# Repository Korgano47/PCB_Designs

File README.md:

# PCB_Designs
This repository contains some PCB examples designed by me with Autodesk EAGLE.

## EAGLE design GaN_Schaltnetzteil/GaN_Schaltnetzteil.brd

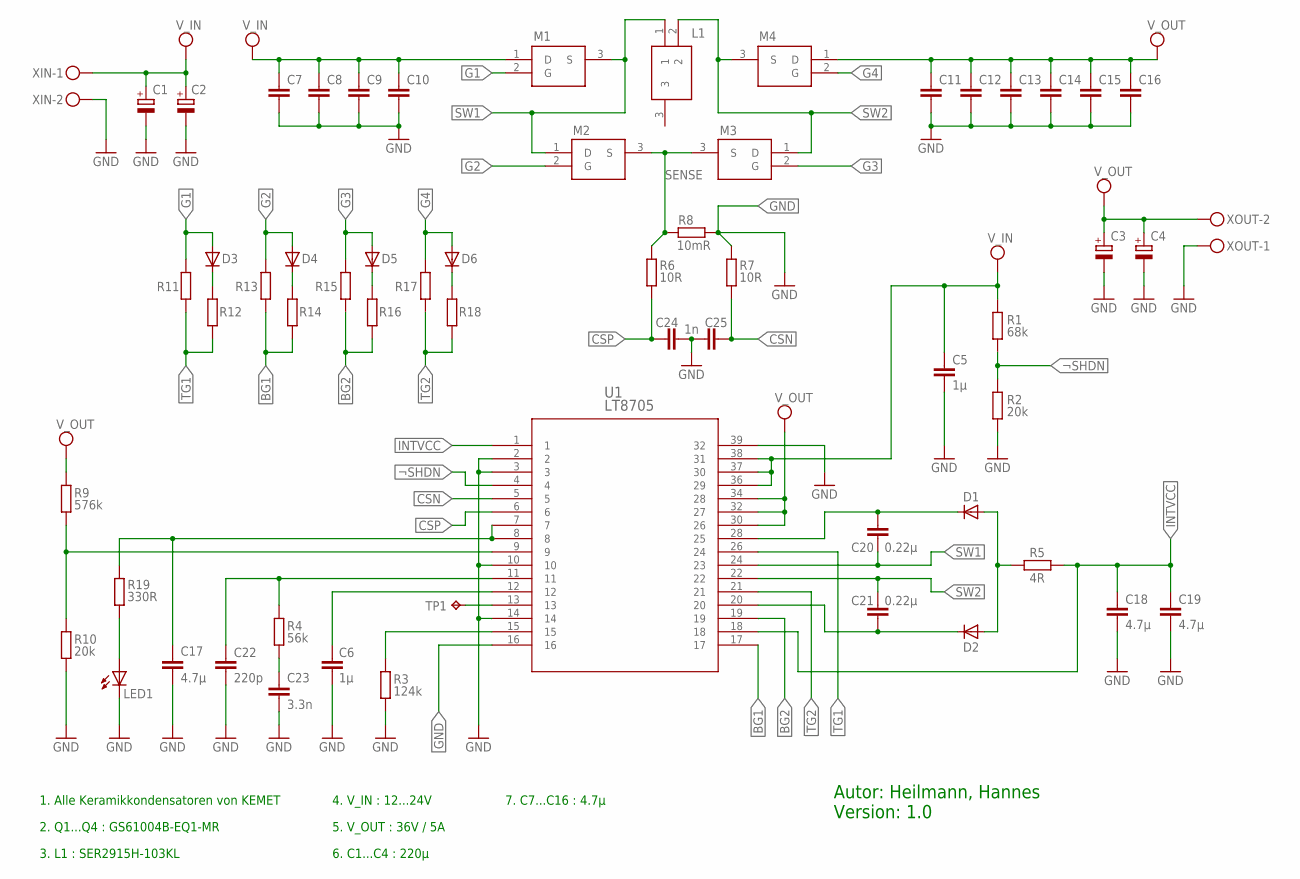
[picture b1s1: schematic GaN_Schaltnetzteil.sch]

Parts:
C1, C2, C3, C4: 220µ; PANASONIC_G
C5, C6: 1µ; C1206K
C7, C8, C9, C10, C11, C12, C13, C14, C15, C16, C17, C18, C19: 4.7µ; C1206K
C20, C21: 0.22µ; C1206K
C22: 220p; C1206K
C23: 3.3n; C1206K
C24, C25: 1n; C1206K
D1, D2, D3, D4, D5, D6: GF1; SMA-DO214AC
L1: SER2915H-103KL; SER2900
LED1: LEDSMT1206; 1206
M1, M2, M3, M4: GS61004B-E01-MR
R1: 68k; R1206
R2, R10: 20k; R1206
R3: 124k; R1206
R4: 56k; R1206
R5: 4R; R1206
R6, R7: 10R; R1206
R8: 10mR; R1206
R9: 576k; R1206
R11, R12, R13, R14, R15, R16, R17, R18: R-EU_R1206; R1206
R19: 330R; R1206
TP1: TPTP08R; TP08R
U1: LT8705; TSSOP-38_FE/AB
XIN: INPUT; W237-102
XOUT: OUTPUT; W237-102

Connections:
BG1: R13.1, R14.1, U1.17
BG2: R15.1, R16.1, U1.19
BOOST1: C20.1, D1.K (C), U1.28 (25)
BOOST2: C21.1, D2.K (C), U1.20
CSN: C25.2, R7.1, U1.5
CSP: C24.1, R6.1, U1.6
G1: D3.A, M1.2 (G), R11.2
G2: D4.A, M2.2 (G), R13.2
G3: D5.A, M3.2 (G), R15.2
G4: D6.A, M4.2 (G), R17.2
GND: C1.-, C2.-, C3.-, C4.-, C5.2, C6.2, C7.2, C8.2, C9.2, C10.2, C11.2, C12.2, C13.2, C14.2, C15.2, C16.2, C17.2, C18.2, C19.2, C22.2, C23.2, C24.2, C25.1, LED1.C, R2.2, R3.1, R7.2, R8.1, R10.2, U1.2, U1.3, U1.10, U1.14, U1.16, U1.39 (32), XIN.2, XOUT.1
INTVCC: C18.1, C19.1, R5.1, U1.1, U1.18
unnamed: LED1.A, R19.1
unnamed: D3.K (C), R12.2
unnamed: D4.K (C), R14.2
unnamed: TP1.TP, U1.13
unnamed: C6.1, U1.12
unnamed: R3.2, U1.15
unnamed: C23.1, R4.2
unnamed: D5.K (C), R16.2
unnamed: C22.1, R4.1, U1.11
unnamed: D6.K (C), R18.2
unnamed: R9.2, R10.1, U1.9
unnamed: D1.A, D2.A, R5.2
unnamed: C17.1, R19.2, U1.7, U1.8
SENSE: M2.3 (S), M3.3 (S), R6.2, R8.2
SW1: C20.2, L1.1, M1.3 (S), M2.1 (D), U1.24 (23)
SW2: C21.2, L1.2, M3.1 (D), M4.3 (S), U1.22
TG1: R11.1, R12.1, U1.26 (24)
TG2: R17.1, R18.1, U1.21
VCC: C1.+, C2.+, C5.1, C7.1, C8.1, C9.1, C10.1, M1.1 (D), R1.1, U1.36 (29), U1.37 (30), U1.38 (31), XIN.1
VDD: C3.+, C4.+, C11.1, C12.1, C13.1, C14.1, C15.1, C16.1, M4.1 (D), R9.1, U1.30 (26), U1.32 (27), U1.34 (28), XOUT.2
¬SHDN: R1.2, R2.1, U1.4

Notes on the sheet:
1. Alle Keramikkondensatoren von KEMET
2. Q1...Q4 : GS61004B-EQ1-MR
Autor: Heilmann, Hannes Version: 1.0
4. V_IN : 12...24V
5. V_OUT : 36V / 5A
7. C7...C16 : 4.7µ
6. C1...C4 : 220µ
3. L1 : SER2915H-103KL

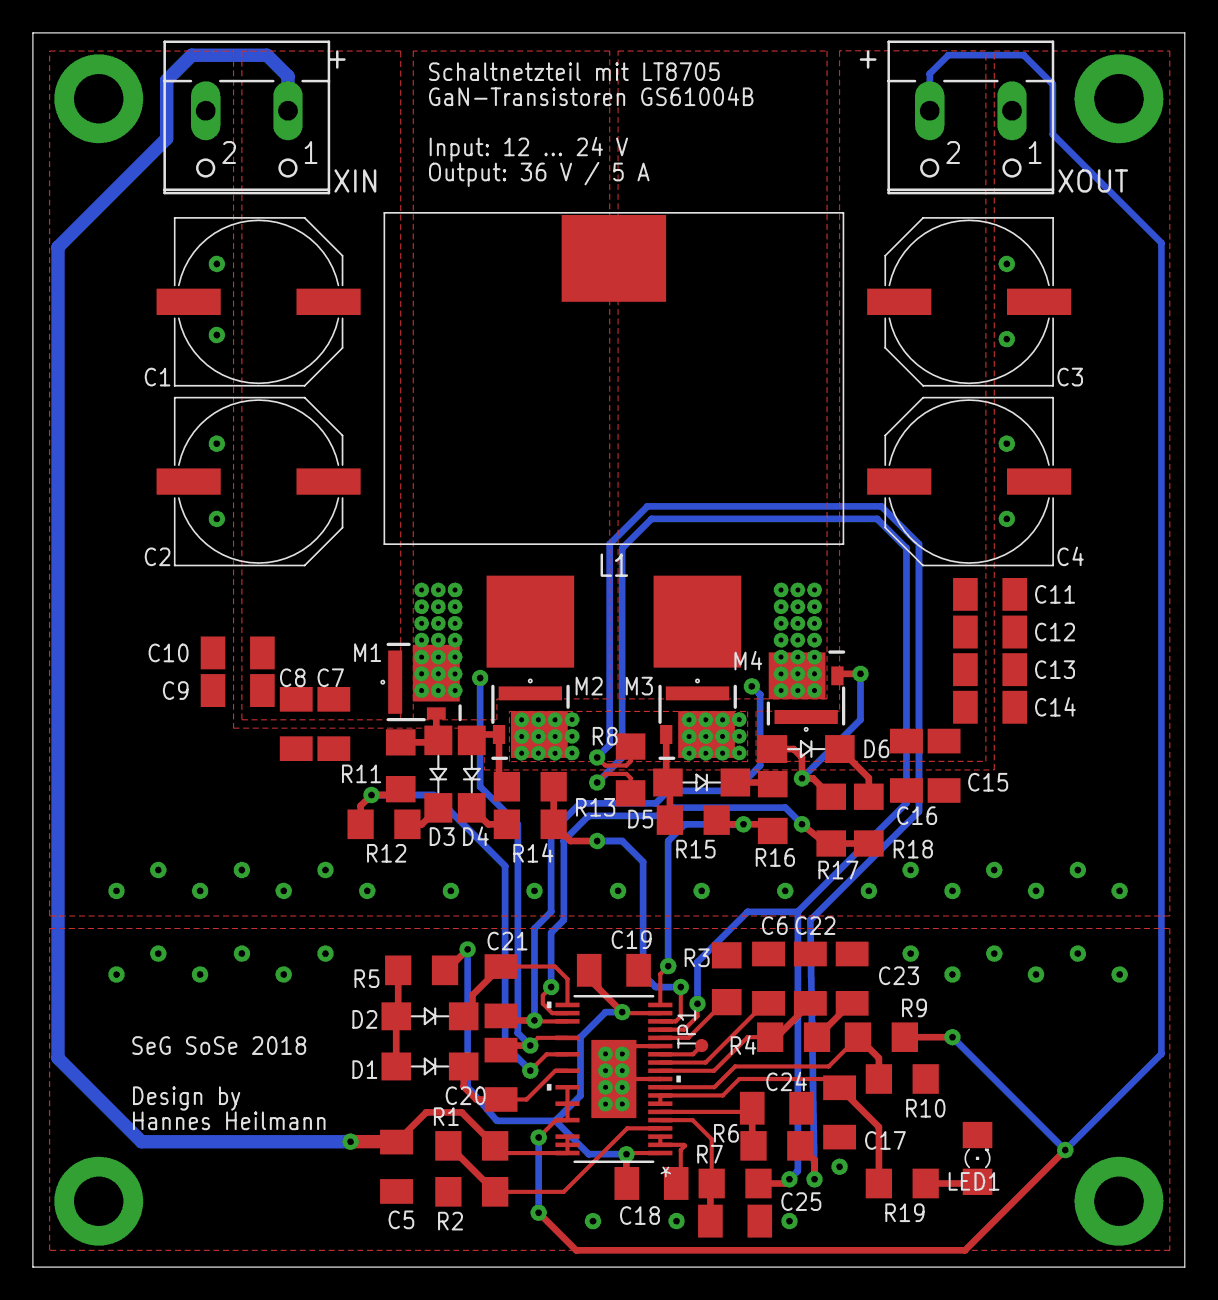
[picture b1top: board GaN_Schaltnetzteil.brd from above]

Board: 2 copper layers, 70.0 x 75.0 mm, 60 parts (0 on the bottom side), 33 nets.

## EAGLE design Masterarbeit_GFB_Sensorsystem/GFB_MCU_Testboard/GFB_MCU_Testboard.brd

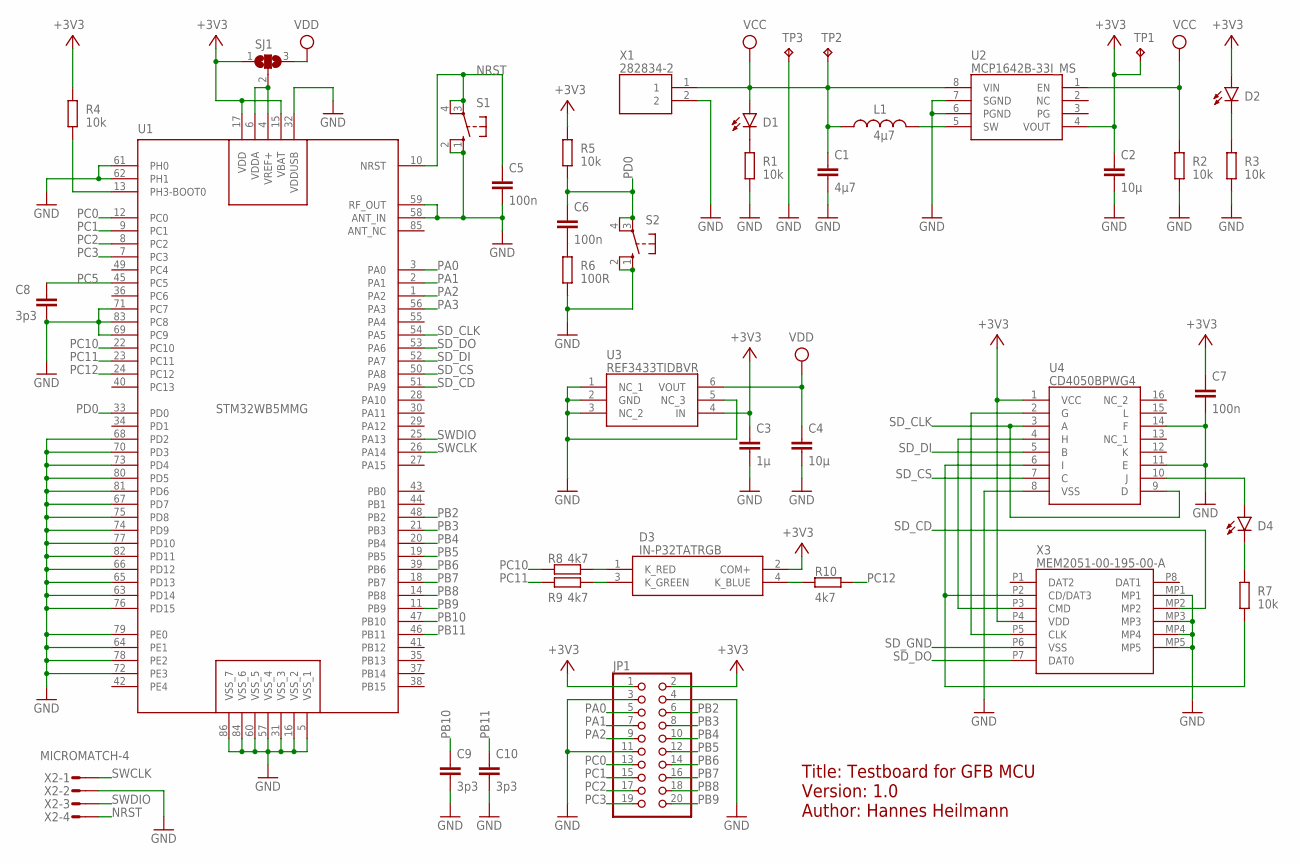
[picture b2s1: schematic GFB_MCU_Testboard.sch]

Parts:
C1: 4µ7; C1206K
C2, C4: 10µ; C1206K
C3: 1µ; C1206K
C5, C6, C7: 100n; C0805K
C8, C9, C10: 3p3; C0805K
D1, D2, D4: LEDSML0805; SML0805
D3: IN-P32TATRGB; INP32TATRGB
JP1: PINHD-2X10; 2X10
L1: 4µ7; L4532P
R1, R2, R3, R4, R5, R7: 10k; R0805
R6: 100R; R0805
R8, R9, R10: 4k7; R0805
S1, S2: 10-XX; B3F-10XX
SJ1: SJ2W; SJ_2
TP1, TP2, TP3: TPB2,54; B2,54
U1: STM32WB5MMG
U2: MCP1642B-33I_MS; SOP65P490X110-8N
U3: REF3433TIDBVR; SOT95P280X145-6N
U4: CD4050BPWG4; SOP65P640X120-16N
X1: 282834-2; 282834-2_1
X2: MICROMATCH-4
X3: MEM2051-00-195-00-A; MEM20510019500A

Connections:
+3V3: C2.1, C3.1, C7.1, D2.A, D3.2 (COM+), JP1.1, JP1.2, R4.1, R5.1, SJ1.1, TP1.TP, U1.15 (VBAT), U1.17 (VDD), U2.4 (VOUT), U3.4 (IN), U4.1 (VCC), X3.P4 (VDD)
GND: C1.2, C2.2, C3.2, C4.2, C5.2, C7.2, C8.2, C9.2, C10.2, JP1.3, JP1.4, JP1.11, R1.2, R2.1, R3.2, R6.2, S1.1 (S), S1.2 (S1), S2.1 (S), S2.2 (S1), TP3.TP, U1.5 (VSS_1), U1.16 (VSS_2), U1.31 (VSS_3), U1.32 (VDDUSB), U1.57 (VSS_4), U1.58 (ANT_IN), U1.59 (RF_OUT), U1.60 (VSS_5), U1.61 (PH0), U1.62 (PH1), U1.63 (PD14), U1.64 (PE1), U1.65 (PD13), U1.66 (PD12), U1.67 (PD7), U1.68 (PD2), U1.69 (PC9), U1.70 (PD3), U1.71 (PC7), U1.72 (PE3), U1.73 (PD4), U1.74 (PD9), U1.75 (PD8), U1.76 (PD15), U1.77 (PD10), U1.78 (PE2), U1.79 (PE0), U1.80 (PD5), U1.81 (PD6), U1.82 (PD11), U1.83 (PC8), U1.84 (VSS_6), U1.86 (VSS_7), U2.6 (PGND), U2.7 (SGND), U3.1 (NC_1), U3.2 (GND), U3.3 (NC_2), U3.5 (NC_3), U4.8 (VSS), U4.11 (E), U4.14 (F), X1.2, X2.2, X3.MP1, X3.MP3, X3.MP4, X3.MP5
unnamed: D2.C, R3.1
unnamed: L1.2, U2.5 (SW)
unnamed: D1.C, R1.1
unnamed: R4.2, U1.13 (PH3-BOOT0)
unnamed: C6.2, R6.1
unnamed: U4.2 (G), X3.P5 (CLK)
unnamed: SJ1.2, U1.4 (VREF+), U1.6 (VDDA)
unnamed: D3.3 (K_GREEN), R9.2
unnamed: D3.1 (K_RED), R8.2
unnamed: D3.4 (K_BLUE), R10.1
unnamed: D4.C, R7.1
unnamed: R7.2, U4.6 (I), X3.P2 (CD/DAT3)
unnamed: U4.4 (H), X3.P3 (CMD)
unnamed: D4.A, U4.10 (J)
NRST: C5.1, S1.3, S1.4 (P1), U1.10 (NRST), X2.4
PA0: JP1.5, U1.3 (PA0)
PA1: JP1.7, U1.2 (PA1)
PA2: JP1.9, U1.1 (PA2)
PA3: U1.56 (PA3)
PB2: JP1.6, U1.48 (PB2)
PB3: JP1.8, U1.21 (PB3)
PB4: JP1.10, U1.20 (PB4)
PB5: JP1.12, U1.19 (PB5)
PB6: JP1.14, U1.39 (PB6)
PB7: JP1.16, U1.18 (PB7)
PB8: JP1.18, U1.14 (PB8)
PB9: JP1.20, U1.11 (PB9)
PB10: C9.1, U1.47 (PB10)
PB11: C10.1, U1.46 (PB11)
PC0: JP1.13, U1.12 (PC0)
PC1: JP1.15, U1.9 (PC1)
PC2: JP1.17, U1.8 (PC2)
PC3: JP1.19, U1.7 (PC3)
PC5: C8.1, U1.45 (PC5)
PC10: R8.1, U1.22 (PC10)
PC11: R9.1, U1.23 (PC11)
PC12: R10.2, U1.24 (PC12)
PD0: C6.1, R5.2, S2.3, S2.4 (P1), U1.33 (PD0)
SD_CD: U1.51 (PA9), X3.MP2
SD_CLK: U1.54 (PA5), U4.3 (A), U4.9 (D)
SD_CS: U1.50 (PA8), U4.7 (C)
SD_DI: U1.52 (PA7), U4.5 (B)
SD_DO: U1.53 (PA6), X3.P7 (DAT0)
SD_GND: X3.P6 (VSS)
SWCLK: U1.26 (PA14), X2.1
SWDIO: U1.25 (PA13), X2.3
VCC: C1.1, D1.A, L1.1, R2.2, TP2.TP, U2.1 (EN), U2.8 (VIN), X1.1
VDD: C4.1, SJ1.3, U3.6 (VOUT)

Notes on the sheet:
Title: Testboard for GFB MCU Version: 1.0 Author: Hannes Heilmann

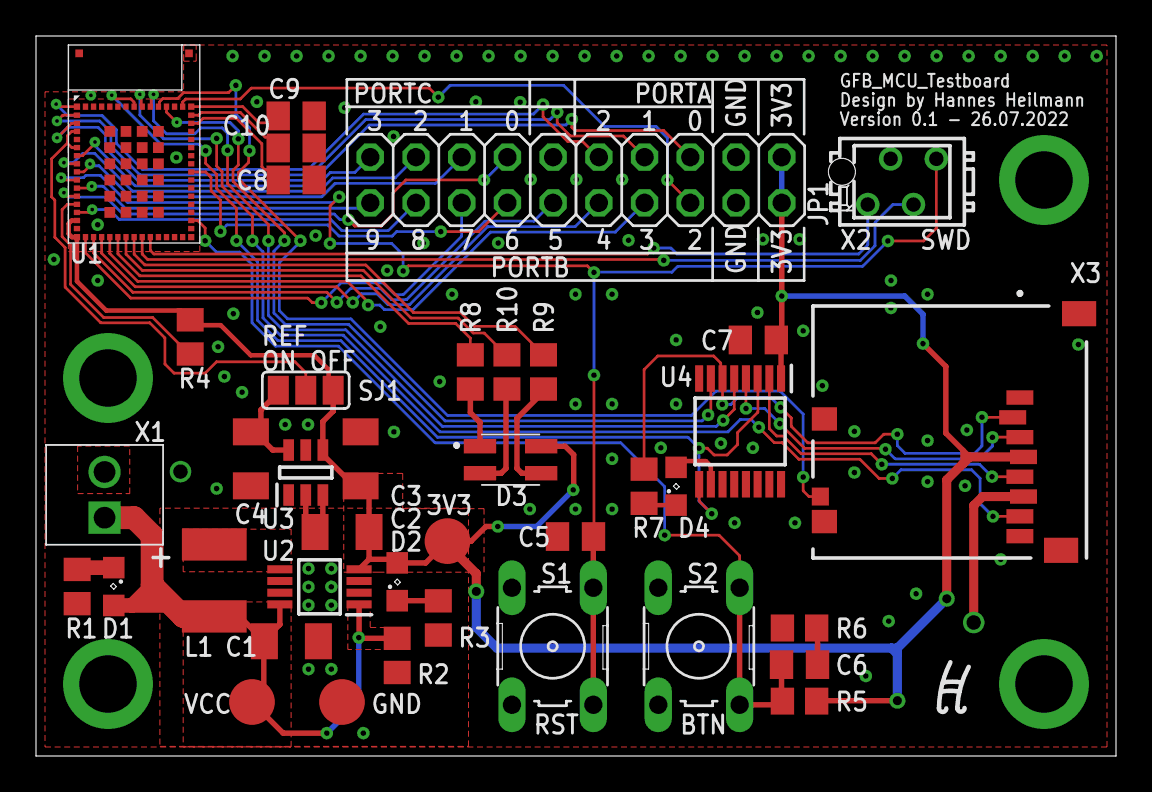
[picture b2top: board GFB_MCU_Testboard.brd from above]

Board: 2 copper layers, 60.0 x 40.0 mm, 39 parts (0 on the bottom side), 48 nets.

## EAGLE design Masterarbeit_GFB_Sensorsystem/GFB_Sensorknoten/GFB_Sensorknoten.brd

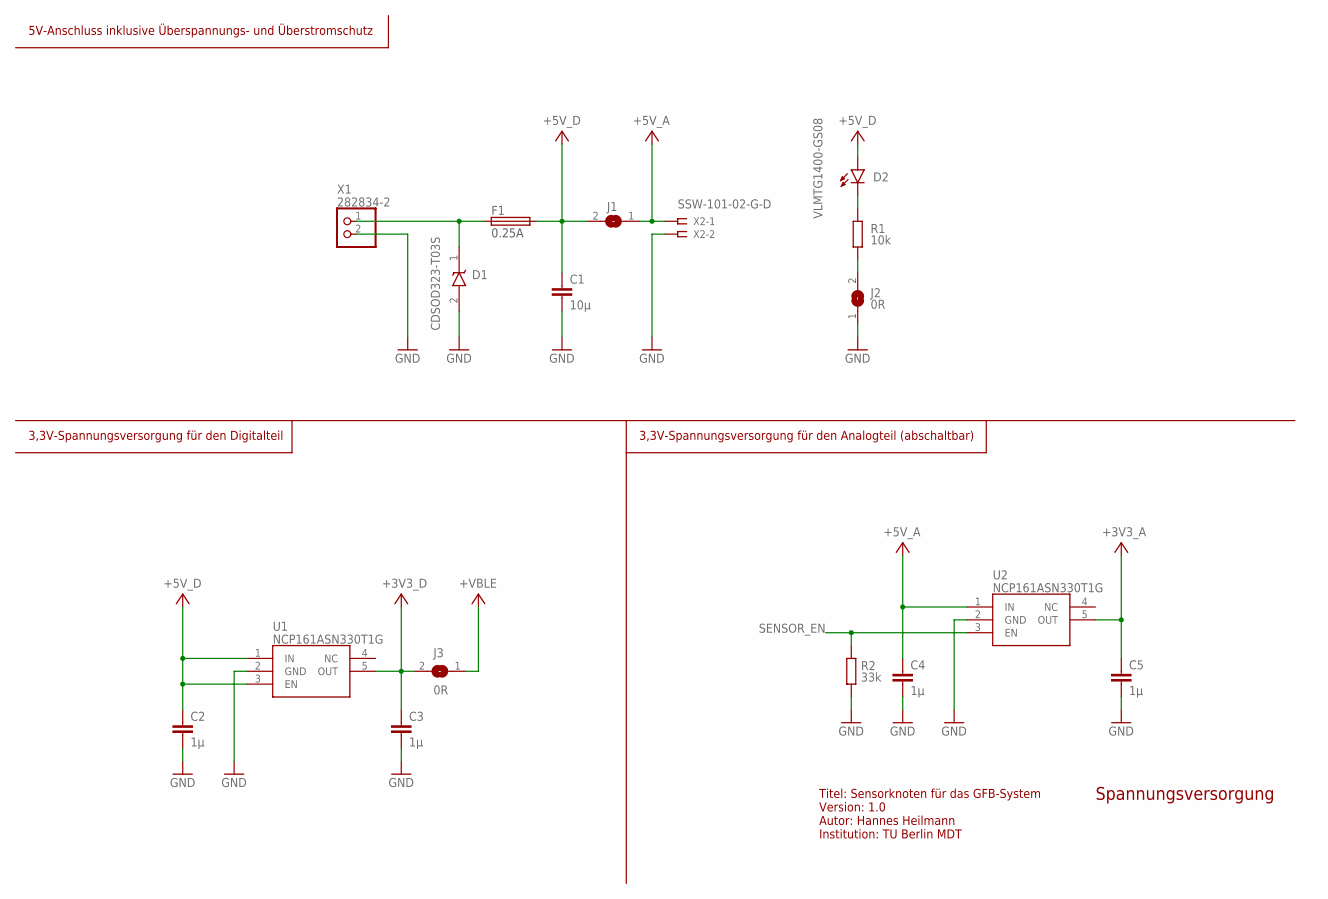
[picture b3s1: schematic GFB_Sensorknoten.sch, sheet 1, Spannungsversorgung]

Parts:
C1: 10µ; PATCHPOLYGRAPHV1_1608M
C2, C3, C4, C5: 1μ; PATCHPOLYGRAPHV1_1608M
D1: CDSOD323-T03S; SOD2513X114N
D2: VLMTG1400-GS08; CHIP-LED0603
F1: SF-0603FP025F-2; R0603
J1: SJ
J2, J3: 0R; PATCHPOLYGRAPHV1_1005M
R1: 10k; PATCHPOLYGRAPHV1_1005M
R2: 33k; PATCHPOLYGRAPHV1_1005M
U1, U2: NCP161ASN330T1G; SOT95P280X145-5N
X1: 282834-2; SHDR2W85P0X254_1X2_554X650X103
X2: SSW-101-02-G-D

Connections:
+3V3_A: C5.1, U2.5 (OUT); also elsewhere on the board
+3V3_D: C3.1, J3.2, U1.5 (OUT); also elsewhere on the board
+5V_A: C4.1, J1.1, U2.1 (IN), X2.1
+5V_D: C1.1, C2.1, D2.A, F1.2, J1.2, U1.1 (IN), U1.3 (EN)
+VBLE: J3.1; also elsewhere on the board
GND: C1.2, C2.2, C3.2, C4.2, C5.2, D1.2 (A), J2.1, R2.1, U1.2 (GND), U2.2 (GND), X1.2, X2.2; also elsewhere on the board
unnamed: J2.2, R1.1
unnamed: D2.C, R1.2
unnamed: D1.1 (K), F1.1, X1.1
SENSOR_EN: R2.2, U2.3 (EN); also elsewhere on the board

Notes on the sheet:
0.25A
Titel: Sensorknoten für das GFB-System Version: 1.0 Autor: Hannes Heilmann Institution: TU Berlin MDT
Spannungsversorgung
5V-Anschluss inklusive Überspannungs- und Überstromschutz
3,3V-Spannungsversorgung für den Digitalteil
3,3V-Spannungsversorgung für den Analogteil (abschaltbar)

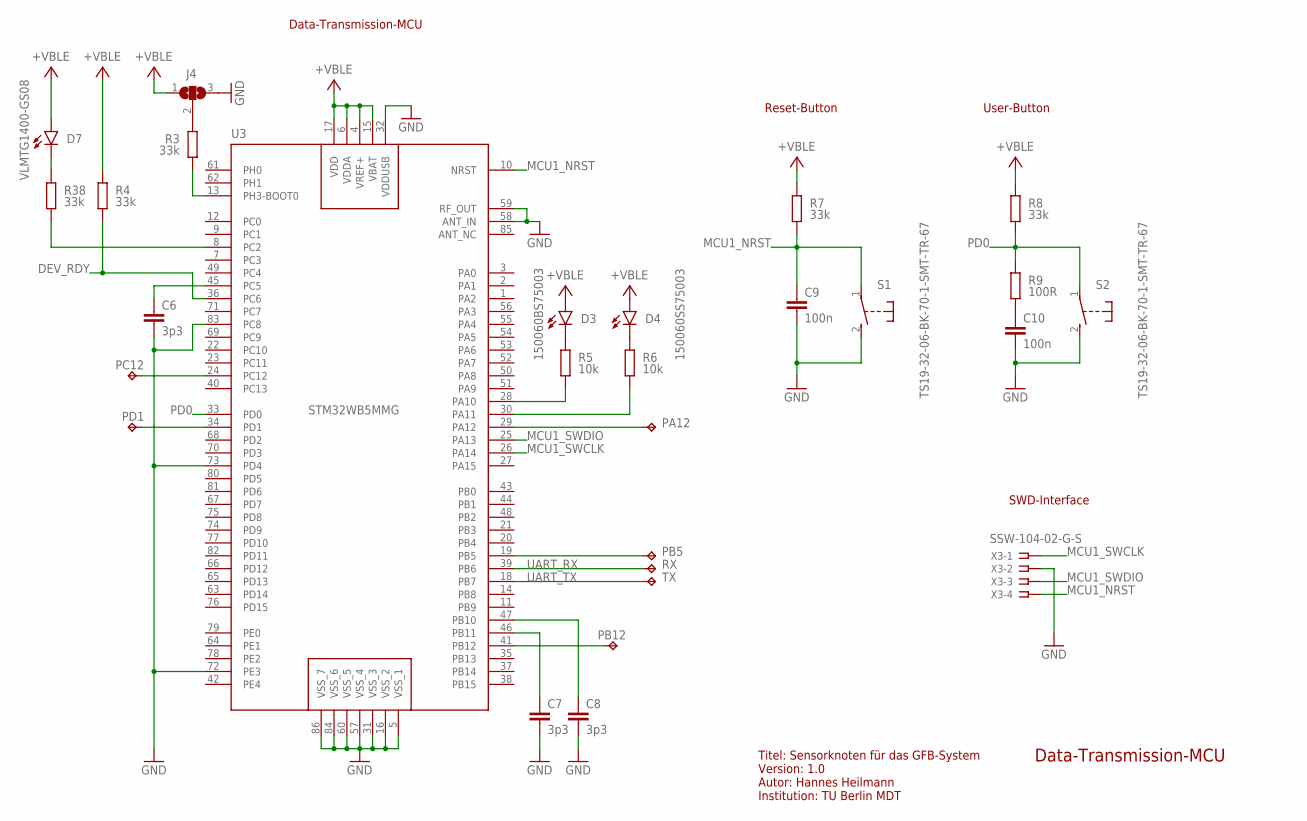
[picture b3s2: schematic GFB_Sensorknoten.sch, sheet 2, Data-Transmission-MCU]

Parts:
C6, C7, C8: 3p3; PATCHPOLYGRAPHV1_1005M
C9, C10: 100n; PATCHPOLYGRAPHV1_1005M
D3: 150060BS75003; CHIP-LED0603
D4: 150060SS75003; CHIP-LED0603
D7: VLMTG1400-GS08; CHIP-LED0603
J4: JUMPER_3JUMPER_3_0402; JUMPER_3_0402
PA12: TPTP06R; TP06R
PB5, PB12: TPTP06R; TP06R
PC12: TPTP06R; TP06R
PD1: TPTP06R; TP06R
R3, R4, R7, R8, R38: 33k; PATCHPOLYGRAPHV1_1005M
R5, R6: 10k; PATCHPOLYGRAPHV1_1005M
R9: 100R; PATCHPOLYGRAPHV1_1005M
RX: TPTP06R; TP06R
S1, S2: TS19-32-06-BK-70-1-SMT-TR-67; TS193206BK701SMTTR67
TX: TPTP06R; TP06R
U3: STM32WB5MMG
X3: SSW-104-02-G-S

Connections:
+VBLE: D3.A, D4.A, D7.A, J4.1, R4.2, R7.2, R8.2, U3.4 (VREF+), U3.6 (VDDA), U3.15 (VBAT), U3.17 (VDD); also elsewhere on the board
DEV_RDY: R4.1, U3.36 (PC6); also elsewhere on the board
GND: C6.2, C7.2, C8.2, C9.2, C10.2, J4.3, S1.2 (S), S2.2 (S), U3.5 (VSS_1), U3.16 (VSS_2), U3.31 (VSS_3), U3.32 (VDDUSB), U3.57 (VSS_4), U3.58 (ANT_IN), U3.59 (RF_OUT), U3.60 (VSS_5), U3.72 (PE3), U3.73 (PD4), U3.83 (PC8), U3.84 (VSS_6), U3.86 (VSS_7), X3.2; also elsewhere on the board
MCU1_NRST: C9.1, R7.1, S1.1, U3.10 (NRST), X3.4
MCU1_SWCLK: U3.26 (PA14), X3.1
MCU1_SWDIO: U3.25 (PA13), X3.3
unnamed: R3.1, U3.13 (PH3-BOOT0)
unnamed: C6.1, U3.45 (PC5)
unnamed: D3.C, R5.2
unnamed: D4.C, R6.2
unnamed: C10.1, R9.1
unnamed: PB12.TP, U3.41 (PB12)
unnamed: PD1.TP, U3.34 (PD1)
unnamed: PC12.TP, U3.24 (PC12)
unnamed: R38.1, U3.8 (PC2)
unnamed: D7.C, R38.2
unnamed: J4.2, R3.2
PA10: R5.1, U3.28 (PA10)
PA11: R6.1, U3.30 (PA11)
PB10: C8.1, U3.47 (PB10)
PB11: C7.1, U3.46 (PB11)
PD0: R8.1, R9.2, S2.1, U3.33 (PD0)
UART_RES_RX: PA12.TP, U3.29 (PA12)
UART_RES_TX: PB5.TP, U3.19 (PB5)
UART_RX: RX.TP, U3.39 (PB6); also elsewhere on the board
UART_TX: TX.TP, U3.18 (PB7); also elsewhere on the board

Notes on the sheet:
Titel: Sensorknoten für das GFB-System Version: 1.0 Autor: Hannes Heilmann Institution: TU Berlin MDT
Data-Transmission-MCU
Reset-Button
User-Button
SWD-Interface

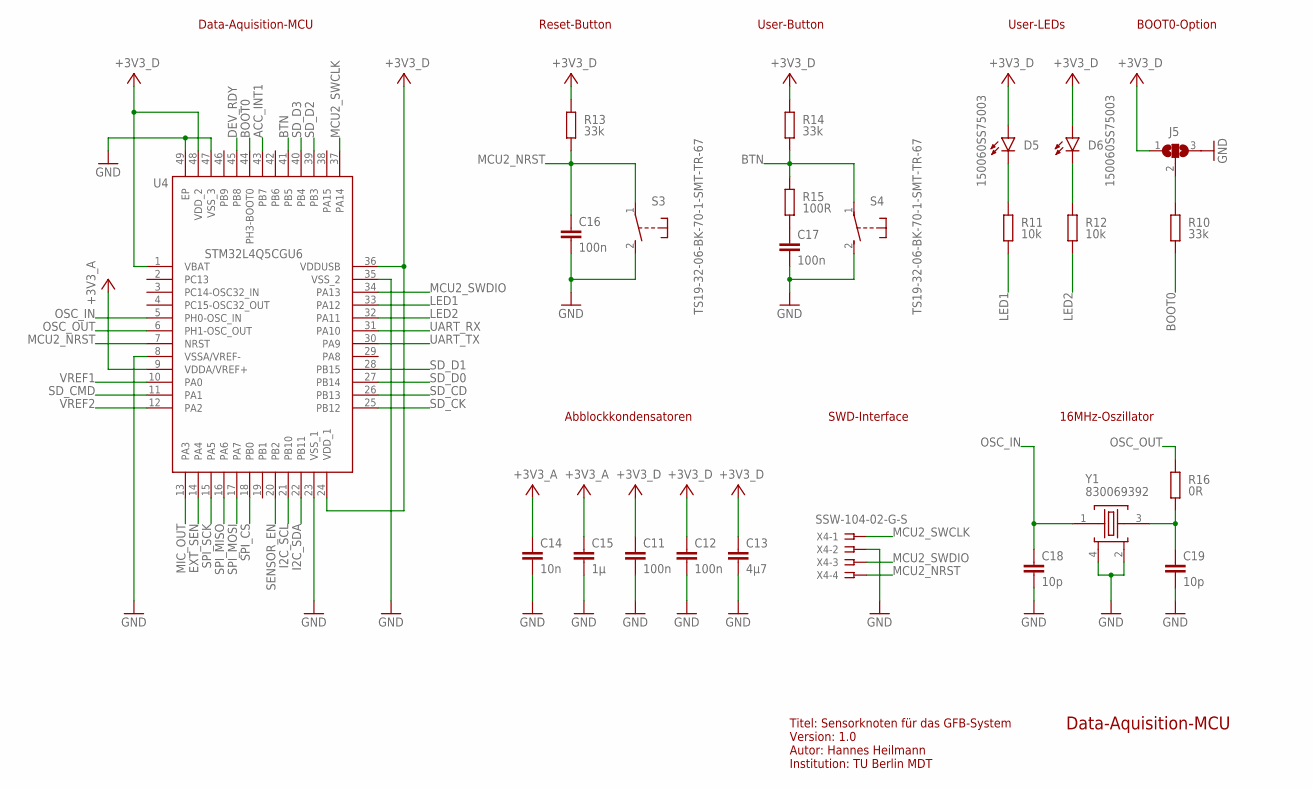
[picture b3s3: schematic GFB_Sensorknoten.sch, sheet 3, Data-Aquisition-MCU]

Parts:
C11, C12, C16, C17: 100n; PATCHPOLYGRAPHV1_1005M
C13: 4µ7; PATCHPOLYGRAPHV1_1608M
C14: 10n; PATCHPOLYGRAPHV1_1005M
C15: 1µ; PATCHPOLYGRAPHV1_1608M
C18, C19: 10p; PATCHPOLYGRAPHV1_1005M
D5, D6: 150060SS75003; CHIP-LED0603
J5: JUMPER_3JUMPER_3_0402; JUMPER_3_0402
R10, R13, R14: 33k; PATCHPOLYGRAPHV1_1005M
R11, R12: 10k; PATCHPOLYGRAPHV1_1005M
R15: 100R; PATCHPOLYGRAPHV1_1005M
R16: 0R; PATCHPOLYGRAPHV1_1005M
S3, S4: TS19-32-06-BK-70-1-SMT-TR-67; TS193206BK701SMTTR67
U4: STM32L4Q5CGU6; QFN50P700X700X65-49N
X4: SSW-104-02-G-S
Y1: 830069392

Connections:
+3V3_A: C14.1, C15.1, U4.9 (VDDA/VREF+); also elsewhere on the board
+3V3_D: C11.1, C12.1, C13.1, D5.A, D6.A, J5.1, R13.2, R14.2, U4.1 (VBAT), U4.24 (VDD_1), U4.36 (VDDUSB), U4.48 (VDD_2); also elsewhere on the board
ACC_INT1: U4.43 (PB7); also elsewhere on the board
BOOT0: R10.1, U4.44 (PH3-BOOT0)
BTN: R14.1, R15.2, S4.1, U4.41 (PB5)
DEV_RDY: U4.45 (PB8); also elsewhere on the board
EXT_SEN: U4.14 (PA4); also elsewhere on the board
GND: C11.2, C12.2, C13.2, C14.2, C15.2, C16.2, C17.2, C18.2, C19.2, J5.3, S3.2 (S), S4.2 (S), U4.8 (VSSA/VREF-), U4.23 (VSS_1), U4.35 (VSS_2), U4.47 (VSS_3), U4.49 (EP), X4.2, Y1.2 (GND_1), Y1.4 (GND_2); also elsewhere on the board
I2C_SCL: U4.21 (PB10); also elsewhere on the board
I2C_SDA: U4.22 (PB11); also elsewhere on the board
LED1: R11.1, U4.33 (PA12)
LED2: R12.1, U4.32 (PA11)
MCU2_NRST: C16.1, R13.1, S3.1, U4.7 (NRST), X4.4
MCU2_SWCLK: U4.37 (PA14), X4.1
MCU2_SWDIO: U4.34 (PA13), X4.3
MIC_OUT: U4.13 (PA3); also elsewhere on the board
unnamed: C17.1, R15.1
unnamed: C19.1, R16.1, Y1.3 (OSC_2)
unnamed: D5.C, R11.2
unnamed: D6.C, R12.2
unnamed: J5.2, R10.2
OSC_IN: C18.1, U4.5 (PH0-OSC_IN), Y1.1 (OSC_1)
OSC_OUT: R16.2, U4.6 (PH1-OSC_OUT)
SD_CD: U4.26 (PB13); also elsewhere on the board
SD_CK: U4.25 (PB12); also elsewhere on the board
SD_CMD: U4.11 (PA1); also elsewhere on the board
SD_D0: U4.27 (PB14); also elsewhere on the board
SD_D1: U4.28 (PB15); also elsewhere on the board
SD_D2: U4.39 (PB3); also elsewhere on the board
SD_D3: U4.40 (PB4); also elsewhere on the board
SENSOR_EN: U4.20 (PB2); also elsewhere on the board
SPI_CS: U4.18 (PB0); also elsewhere on the board
SPI_MISO: U4.16 (PA6); also elsewhere on the board
SPI_MOSI: U4.17 (PA7); also elsewhere on the board
SPI_SCK: U4.15 (PA5); also elsewhere on the board
UART_RX: U4.31 (PA10); also elsewhere on the board
UART_TX: U4.30 (PA9); also elsewhere on the board
VREF1: U4.10 (PA0); also elsewhere on the board
VREF2: U4.12 (PA2); also elsewhere on the board

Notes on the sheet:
Titel: Sensorknoten für das GFB-System Version: 1.0 Autor: Hannes Heilmann Institution: TU Berlin MDT
Data-Aquisition-MCU
Reset-Button
User-Button
User-LEDs
BOOT0-Option
Abblockkondensatoren
16MHz-Oszillator
SWD-Interface

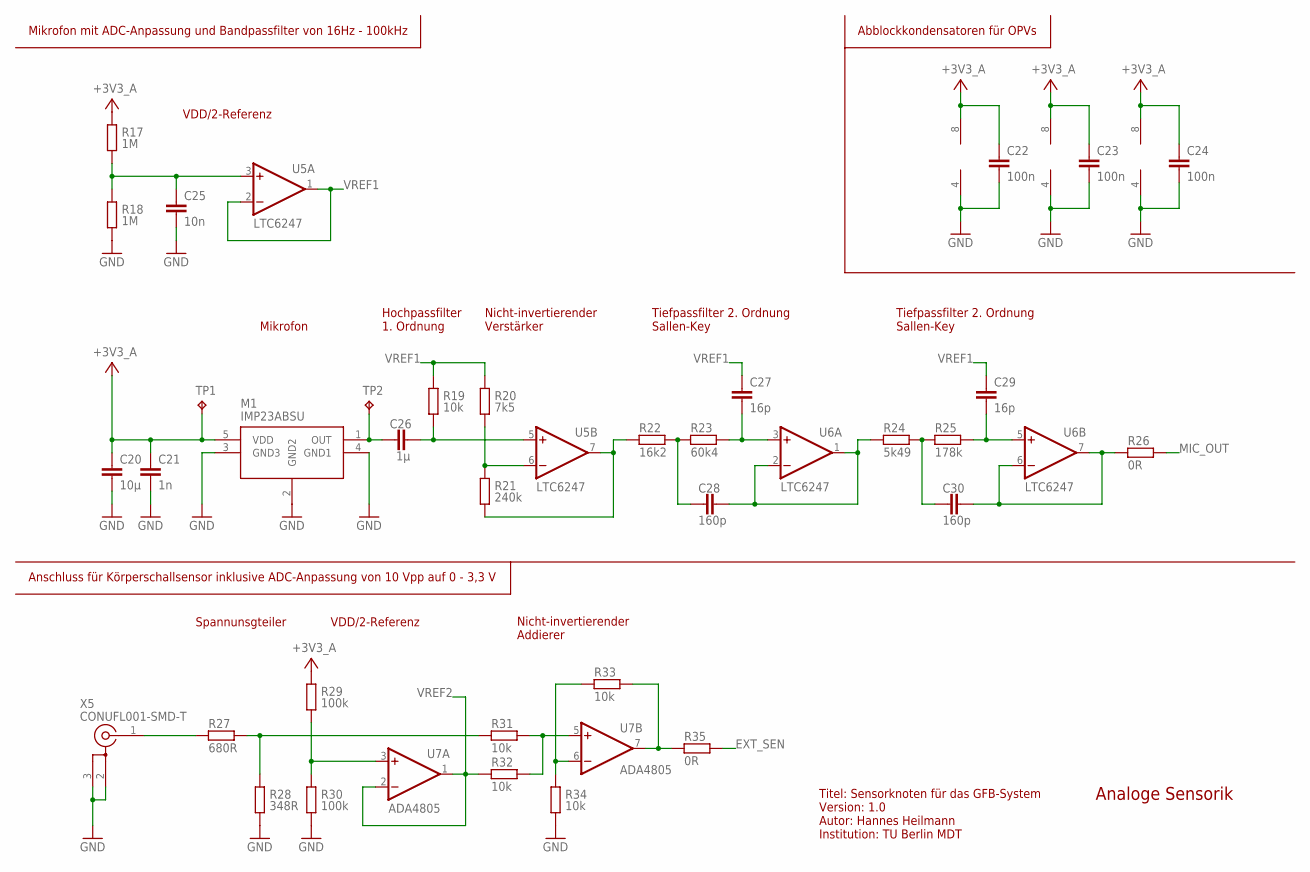
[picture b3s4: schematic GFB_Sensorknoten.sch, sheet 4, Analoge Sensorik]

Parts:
C20: 10µ; PATCHPOLYGRAPHV1_1608M
C21: 1n; PATCHPOLYGRAPHV1_1005M
C22, C23, C24: 100n; PATCHPOLYGRAPHV1_1005M
C25: 10n; PATCHPOLYGRAPHV1_1005M
C26: 1µ; PATCHPOLYGRAPHV1_1608M
C27, C29: 16p; PATCHPOLYGRAPHV1_1005M
C28, C30: 160p; PATCHPOLYGRAPHV1_1005M
M1: IMP23ABSU
R17, R18: 1M; PATCHPOLYGRAPHV1_1005M
R19, R31, R32, R33, R34: 10k; PATCHPOLYGRAPHV1_1005M
R20: 7k5; PATCHPOLYGRAPHV1_1005M
R21: 240k; PATCHPOLYGRAPHV1_1005M
R22: 16k2; PATCHPOLYGRAPHV1_1005M
R23: 60k4; PATCHPOLYGRAPHV1_1005M
R24: 5k49; PATCHPOLYGRAPHV1_1005M
R25: 178k; PATCHPOLYGRAPHV1_1005M
R26, R35: 0R; PATCHPOLYGRAPHV1_1005M
R27: 680R; PATCHPOLYGRAPHV1_1005M
R28: 348R; PATCHPOLYGRAPHV1_1005M
R29, R30: 100k; PATCHPOLYGRAPHV1_1005M
TP1, TP2: TPTP06R; TP06R
U5, U6: LTC6247; SOP65P490X110-8N
U7: ADA4805; SOP65P490X110-8N
X5: CONUFL001-SMD-T; CONUFL001-SMD

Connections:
+3V3_A: C20.1, C21.1, C22.1, C23.1, C24.1, M1.5 (VDD), R17.2, R29.2, TP1.TP, U5.8 (V+), U6.8 (V+), U7.8 (V+); also elsewhere on the board
EXT_SEN: R35.1; also elsewhere on the board
GND: C20.2, C21.2, C22.2, C23.2, C24.2, C25.2, M1.2 (GND2), M1.3 (GND3), M1.4 (GND1), R18.1, R28.1, R30.1, R34.1, U5.4 (V-), U6.4 (V-), U7.4 (V-), X5.2 (GND_1), X5.3 (GND_2); also elsewhere on the board
MIC_OUT: R26.1; also elsewhere on the board
MIC_Q0: C26.2, R19.1, U5.5 (+IN)
MIC_Q1: R21.1, R22.1, U5.7 (OUT)
MIC_Q2: C28.1, R24.2, U6.1 (OUT), U6.2 (-IN)
unnamed: C26.1, M1.1 (OUT), TP2.TP
unnamed: C25.1, R17.1, R18.2, U5.3 (+IN)
unnamed: R20.1, R21.2, U5.6 (-IN)
unnamed: C28.2, R22.2, R23.1
unnamed: C29.2, R25.1, U6.5 (+IN)
unnamed: C27.2, R23.2, U6.3 (+IN)
unnamed: R27.1, X5.1 (SIG)
unnamed: C30.2, R24.1, R25.2
unnamed: R27.2, R28.2, R31.1
unnamed: R29.1, R30.2, U7.3 (+IN)
unnamed: R33.1, R34.2, U7.6 (-IN)
unnamed: R31.2, R32.2, U7.5 (+IN)
unnamed: C30.1, R26.2, U6.6 (-IN), U6.7 (OUT)
unnamed: R33.2, R35.2, U7.7 (OUT)
VREF1: C27.1, C29.1, R19.2, R20.2, U5.1 (OUT), U5.2 (-IN); also elsewhere on the board
VREF2: R32.1, U7.1 (OUT), U7.2 (-IN); also elsewhere on the board

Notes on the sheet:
Titel: Sensorknoten für das GFB-System Version: 1.0 Autor: Hannes Heilmann Institution: TU Berlin MDT
Analoge Sensorik
Anschluss für Körperschallsensor inklusive ADC-Anpassung von 10 Vpp auf 0 - 3,3 V
Mikrofon mit ADC-Anpassung und Bandpassfilter von 16Hz - 100kHz
Abblockkondensatoren für OPVs
Mikrofon
Hochpassfilter 1. Ordnung
Nicht-invertierender Verstärker
Tiefpassfilter 2. Ordnung Sallen-Key
Spannunsgteiler
VDD/2-Referenz
Nicht-invertierender Addierer

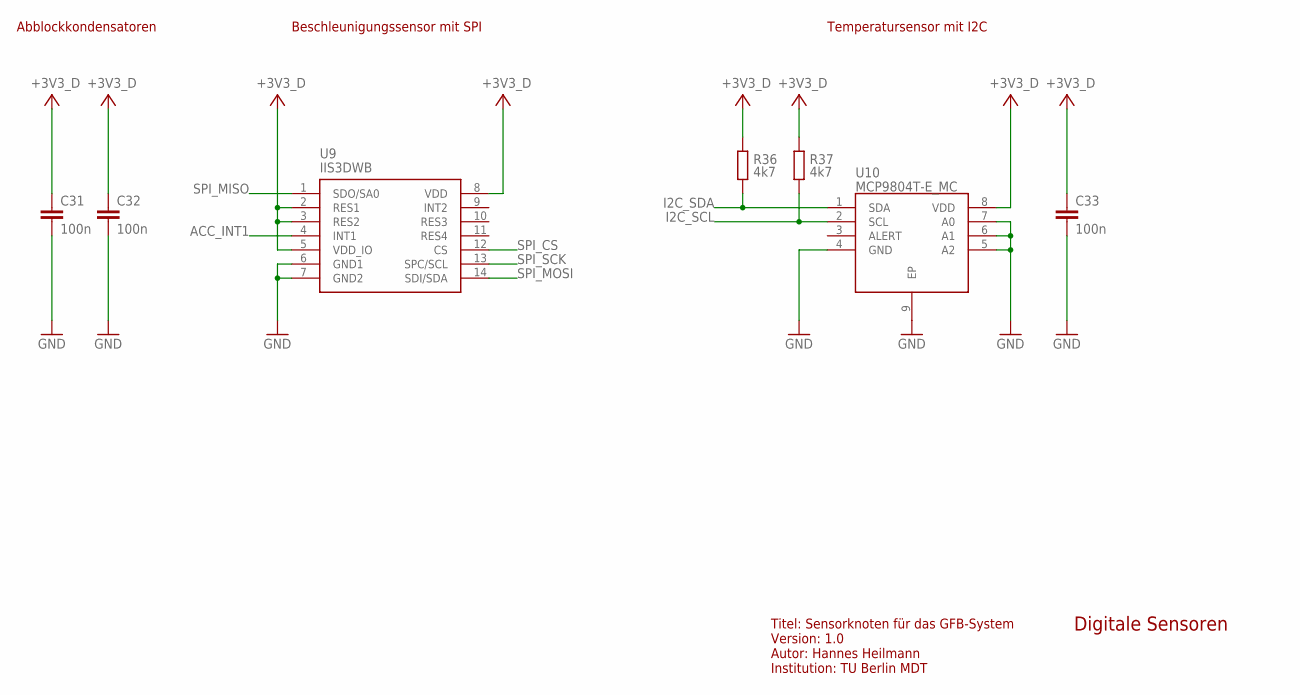
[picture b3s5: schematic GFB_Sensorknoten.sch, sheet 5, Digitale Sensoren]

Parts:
C31, C32, C33: 100n; PATCHPOLYGRAPHV1_1005M
R36, R37: 4k7; PATCHPOLYGRAPHV1_1005M
U9: IIS3DWB
U10: MCP9804T-E_MC; SON50P300X200X100-9N

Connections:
+3V3_D: C31.1, C32.1, C33.1, R36.2, R37.2, U9.2 (RES1), U9.3 (RES2), U9.5 (VDD_IO), U9.8 (VDD), U10.8 (VDD); also elsewhere on the board
ACC_INT1: U9.4 (INT1); also elsewhere on the board
GND: C31.2, C32.2, C33.2, U9.6 (GND1), U9.7 (GND2), U10.4 (GND), U10.5 (A2), U10.6 (A1), U10.7 (A0), U10.9 (EP); also elsewhere on the board
I2C_SCL: R37.1, U10.2 (SCL); also elsewhere on the board
I2C_SDA: R36.1, U10.1 (SDA); also elsewhere on the board
SPI_CS: U9.12 (CS); also elsewhere on the board
SPI_MISO: U9.1 (SDO/SA0); also elsewhere on the board
SPI_MOSI: U9.14 (SDI/SDA); also elsewhere on the board
SPI_SCK: U9.13 (SPC/SCL); also elsewhere on the board

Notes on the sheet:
Titel: Sensorknoten für das GFB-System Version: 1.0 Autor: Hannes Heilmann Institution: TU Berlin MDT
Digitale Sensoren
Abblockkondensatoren
Beschleunigungssensor mit SPI
Temperatursensor mit I2C

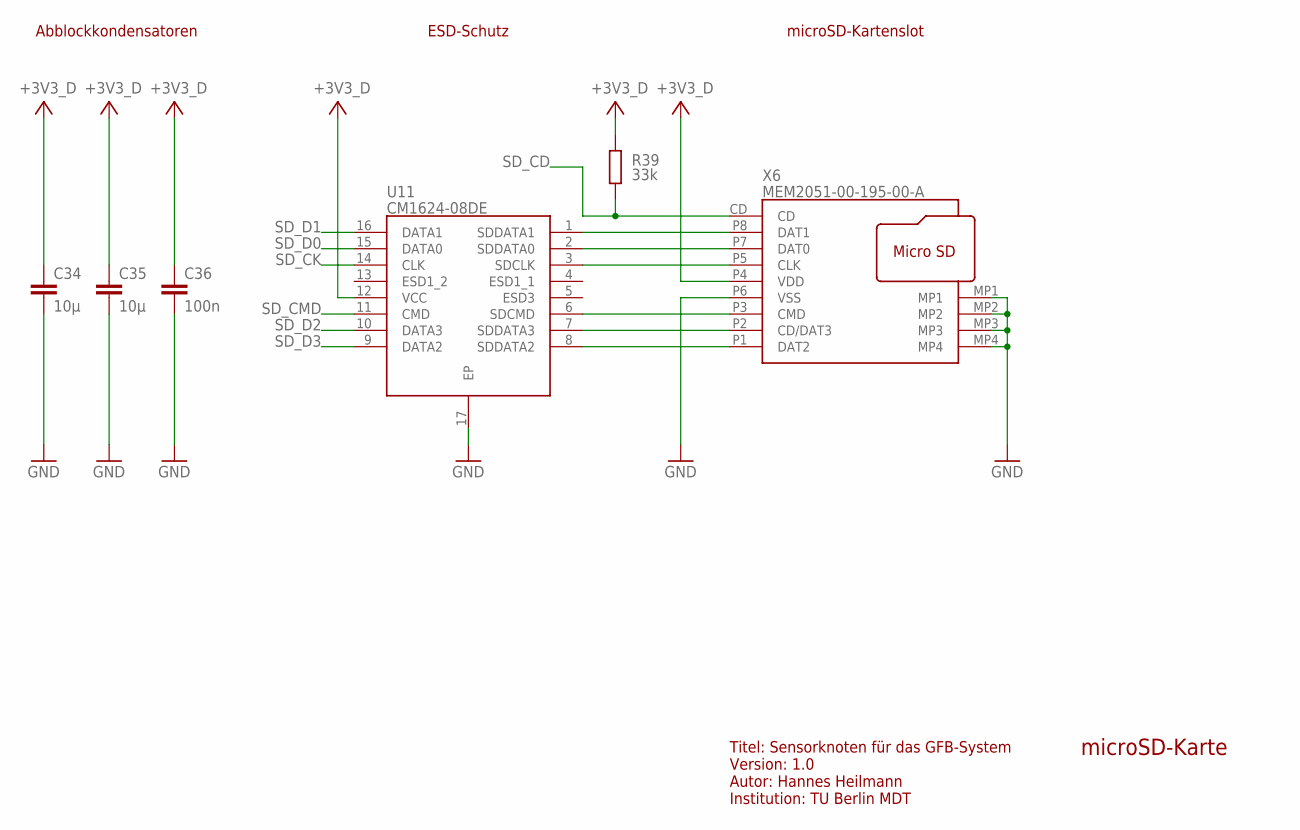
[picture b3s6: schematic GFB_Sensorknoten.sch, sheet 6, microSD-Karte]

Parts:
C34, C35: 10μ; PATCHPOLYGRAPHV1_1608M
C36: 100n; PATCHPOLYGRAPHV1_1005M
R39: 33k; PATCHPOLYGRAPHV1_1005M
U11: CM1624-08DE; SON40P135X330X55-17N
X6: MEM2051-00-195-00-A; MEM20510019500A

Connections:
+3V3_D: C34.1, C35.1, C36.1, R39.2, U11.12 (VCC), X6.P4 (VDD); also elsewhere on the board
GND: C34.2, C35.2, C36.2, U11.17 (EP), X6.MP1, X6.MP2, X6.MP3, X6.MP4, X6.P6 (VSS); also elsewhere on the board
unnamed: U11.1 (SDDATA1), X6.P8 (DAT1)
unnamed: U11.3 (SDCLK), X6.P5 (CLK)
unnamed: U11.7 (SDDATA3), X6.P2 (CD/DAT3)
unnamed: U11.8 (SDDATA2), X6.P1 (DAT2)
unnamed: U11.2 (SDDATA0), X6.P7 (DAT0)
unnamed: U11.6 (SDCMD), X6.P3 (CMD)
SD_CD: R39.1, X6.CD; also elsewhere on the board
SD_CK: U11.14 (CLK); also elsewhere on the board
SD_CMD: U11.11 (CMD); also elsewhere on the board
SD_D0: U11.15 (DATA0); also elsewhere on the board
SD_D1: U11.16 (DATA1); also elsewhere on the board
SD_D2: U11.10 (DATA3); also elsewhere on the board
SD_D3: U11.9 (DATA2); also elsewhere on the board

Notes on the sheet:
Titel: Sensorknoten für das GFB-System Version: 1.0 Autor: Hannes Heilmann Institution: TU Berlin MDT
microSD-Karte
microSD-Kartenslot
ESD-Schutz
Abblockkondensatoren

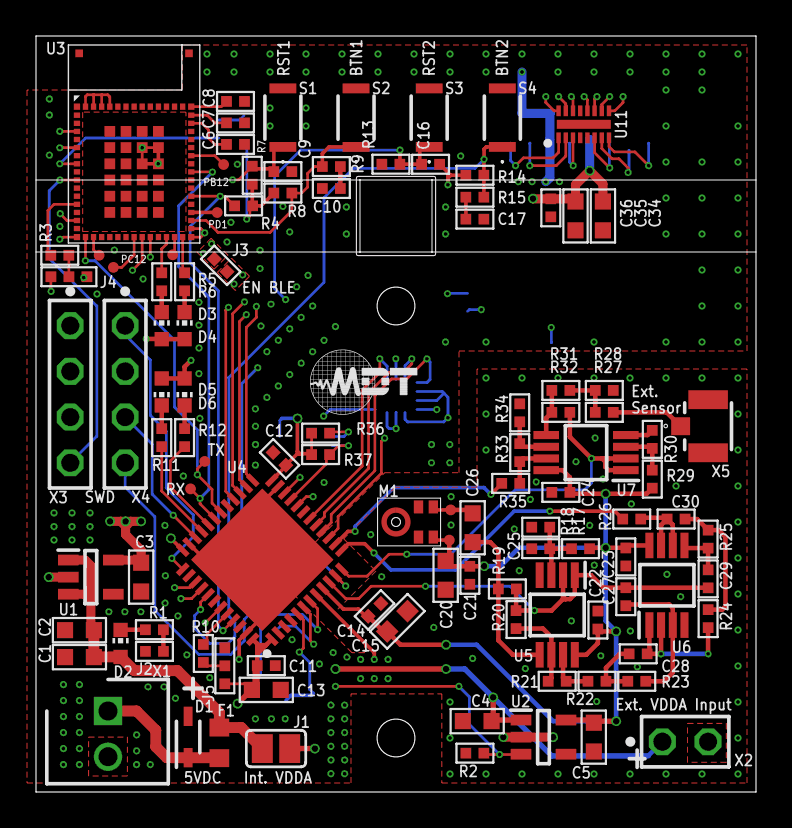
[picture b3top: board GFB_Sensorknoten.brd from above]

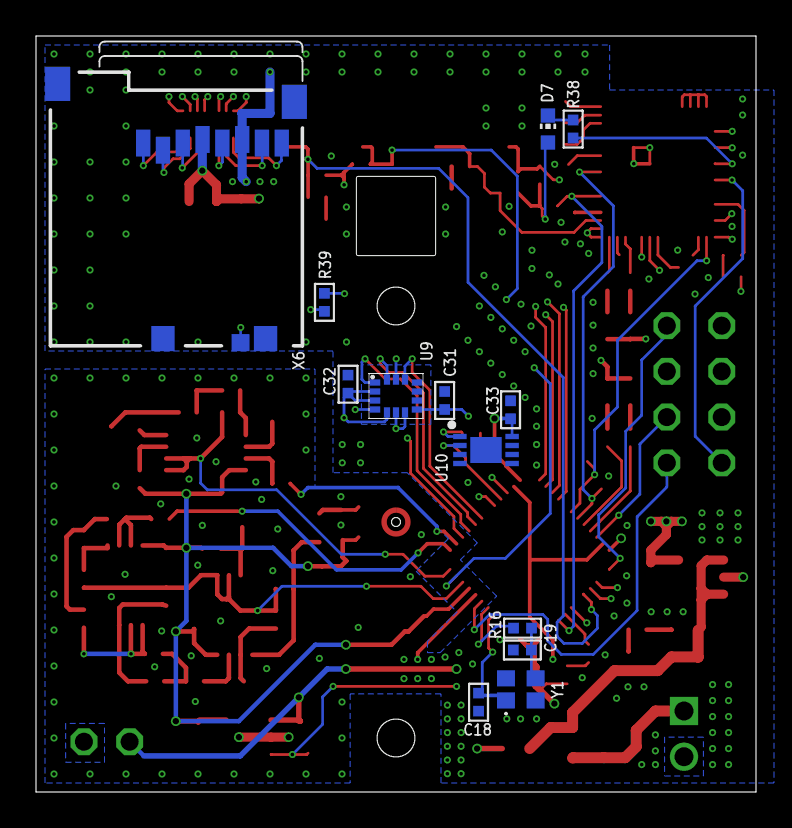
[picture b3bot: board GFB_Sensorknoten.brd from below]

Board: 4 copper layers, 40.0 x 42.0 mm, 119 parts (13 on the bottom side), 89 nets.

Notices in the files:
Bachelorarbeit_WeatherLightSystem/WeatherLight_Coordinator/WeatherLightCoord.brd:
© Design by Hannes Heilmann
